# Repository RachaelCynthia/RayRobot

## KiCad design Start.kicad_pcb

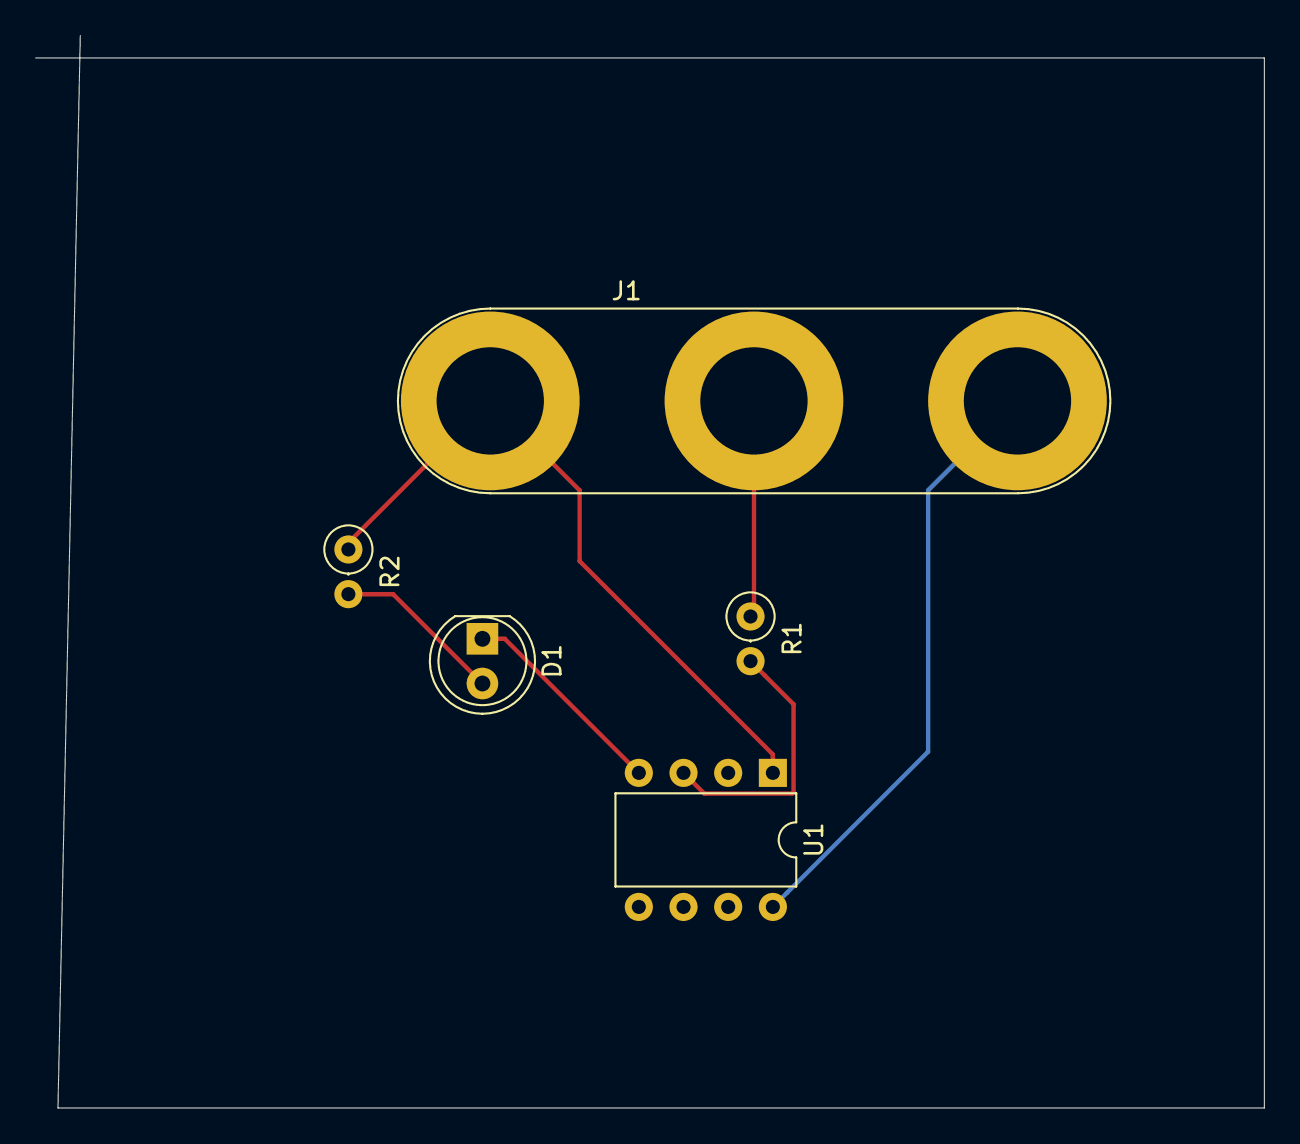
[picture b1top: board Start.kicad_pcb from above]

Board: 2 copper layers, 69.9 x 61.0 mm, 5 parts (0 on the bottom side), 6 nets.

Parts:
D1: LED; LED_D5.0mm
J1: MYCONN3; Banana_Jack_3Pin
R1: 100; R_Axial_DIN0207_L6.3mm_D2.5mm_P2.54mm_Vertical
R2: 1k; R_Axial_DIN0207_L6.3mm_D2.5mm_P2.54mm_Vertical
U1: PIC12C508A-ISN; DIP-8_W7.62mm

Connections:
/INPUT: R1.2, U1.3
/INPUTtoR: J1.2, R1.1
/LEDtoR: D1.2, R2.2
/uCtoLED: D1.1, U1.4
GND: J1.3, U1.8
VCC: J1.1, R2.1, U1.1
